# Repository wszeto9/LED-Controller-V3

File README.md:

# LED-Controller-V3
Version 3 of a easy-to-deploy, low-cost PCBA to control LED lights over Wi-Fi. Designed for use at MIT's East Campus REX event to light up large forts and structures at distances of over 28 ft.

[Interactive BOM](https://htmlpreview.github.io/?https://raw.githubusercontent.com/wszeto9/LED-Controller-V3/main/Documentation/bom/ibom.html)

[PDF Schematic](https://github.com/wszeto9/LED-Controller-V3/blob/main/PCB/LED_Controller_V3.pdf)

**Features:**

- All surface-mount components are basic components that can be placed with JLCPCB's SMT service
- All components that require hand-soldering are through-hole

- Power is transmitted through 14' long ethernet cables to simplify wiring

- Power Input is fused with Mini Blade Fuses

**High-Level Power Distribution Plan**

1. MIT Electric installs a Spider Box that is approximately 50 ft. away from the structure. The Spider Box has numerous 120V outlets that can be used to pull power for the lights.

2. Extension cords are ran from the Spider Box to the DJ Station, as well as other points on the structure as needed. 

3. Power supples (24V/16A, AC to DC) are wired up to the extension cords at all locations that need power. 

4. Each node has a 24V to 5V DC-DC buck converter. This supplies the 5V for all microcontrollers. 

5. 24V and 5V are wired into the power distribution PCB

6. Ethernet cables are run between the power distrubution PCB and nodes. Each node consists of an LED Controller board(this project) and a strip of lights.

**Power Input** 

The Power Distrubution PCB has jumpers that determine the voltage that the LED Controller receives. The LED Power Voltage shall be the same as the LEDs' rated voltage. For instance, 12V Addressible LEDs need 12V Power. The Power Distribution PCB also distributes 5V through the same Ethernet cable. This powers the ESP for changing lighting configurations over Wi-Fi. 

**Fuses** 

This board fuses the LED Power to protect the traces and wires from potential shorts. It is suggested to populate the fuse with one that is rated for 1.5x its current consumption at full brightness. Please note, the RJ45 Connector is rated for 1.5A per connector, for a total of 4.5A for LED Power and 3A for 5V. For this reason, fuses shall not exceed 5A. 

**LED Indicators**

If the board is fully functional, the following LEDs should be continuously lit:

- VCC shall be lit if VCC is higher than 5V and 5V is present

- 5V shall be lit if 5V is present

- 3.3V shall be lit if the 3.3V LDO is populated and 3.3V is present

**Optional to Populate**
- The 5V Buck converter does not need to be populated if the distribution PCB supplies 5V. 

- The 3.3V LDO does not need to be populated if the MCU has a reliable 3.3V LDO built-in. In this case, remove R4 and jump R3.

**Pinouts and Outputs**

Follow the table to set the correct pins to control the LEDs. Both the Wemos D1 and S2 mini are compatable with the Control Board. 
| Wemos D1 GPIO Pin| S2 Mini GPIO Pin| Function |
| -----------------|-----------------| -------- |
| 4|33|Addressible LED 1|
| 5|35|Addressible LED 2|
|14|7 |Analog White
|12|9|Analog Blue
|13|11|Analog Red
|15|12|Analog Green

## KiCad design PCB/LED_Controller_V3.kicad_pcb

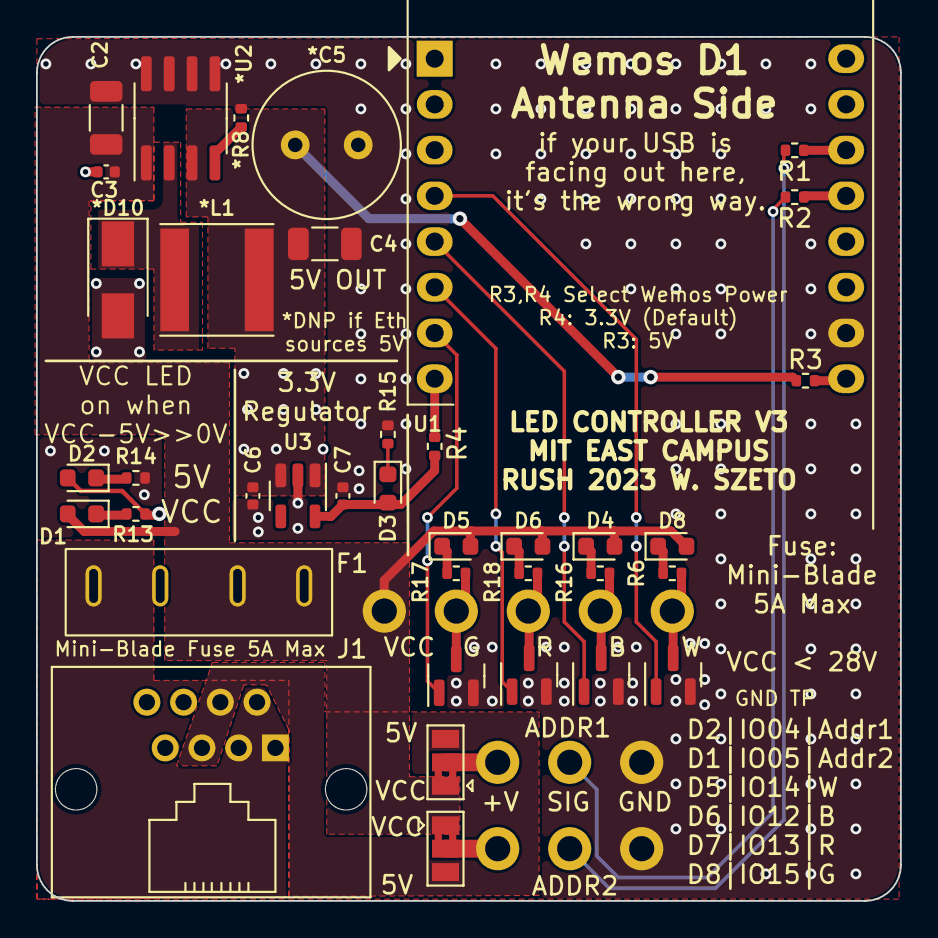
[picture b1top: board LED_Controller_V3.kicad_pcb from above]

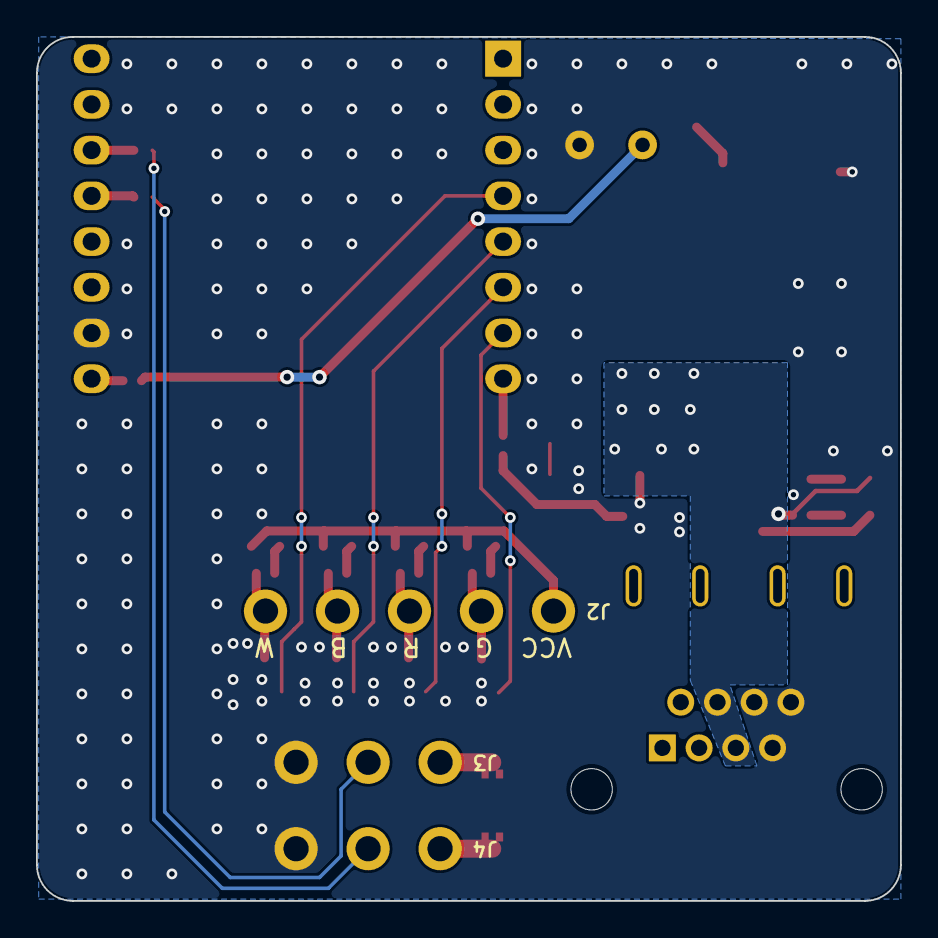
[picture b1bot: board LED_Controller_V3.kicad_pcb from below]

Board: 2 copper layers, 48.0 x 48.0 mm, 41 parts (3 on the bottom side), 30 nets.

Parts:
*C5: 180uF/35V; C_Radial_D8.0mm_H7.0mm_P3.50mm
*D10: SS210; D_SMA
*L1: 68uH/1A; L_Taiyo-Yuden_NR-60xx
*R8: 0R; R_0402_1005Metric
*U2: XL1509; SOIC-8_3.9x4.9mm_P1.27mm
C2, C4: 10uF/50V; C_1206_3216Metric
C3: 100nF/50V; C_0402_1005Metric
C6, C7: 10uF; C_0402_1005Metric
D1: LED_WHITE; LED_0603_1608Metric
D2: LED_RED; LED_0603_1608Metric
D3: LED_GREEN; LED_0603_1608Metric
D4: LED_B; LED_0603_1608Metric
D5: LED_G; LED_0603_1608Metric
D6: LED_R; LED_0603_1608Metric
D8: LED_W; LED_0603_1608Metric
F1: Fuse; XF-506P
J1: RJ45; RJ45_5501-88011111
J2: GRBW; 1x05_16AWG_Wire2Board
J3, J4: Conn_01x03; 1x03_16AWG_Wire2Board
JP1, JP2: VoltageSelector; SolderJumper-3_P1.3mm_Bridged2Bar12_Pad1.0x1.5mm
Q1, Q2, Q3, Q4: AO3400A; SOT-23
R1, R2: 220R; R_0402_1005Metric
R3: DNP; R_0402_1005Metric
R4: 0R; R_0402_1005Metric
R6, R16, R17, R18: 8.2k; R_0402_1005Metric
R13: 2K; R_0402_1005Metric
R14: 1K; R_0402_1005Metric
R15: 330R; R_0402_1005Metric
U1: WeMos_D1_mini; WEMOS_D1_mini_light
U3: XC6210B332MR; SOT-23-5

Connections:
+3V3: C7.1, D3.2 (A), R4.1, U3.5 (VOUT)
+5V: *C5.1, *L1.2, *U2.3 (FB), C4.2, C6.1, D2.2 (A), J1.4, J1.5, JP1.3 (B), JP2.3 (B), R3.1, R13.2, U3.1 (VIN), U3.3 (CE)
/ARGB1: J3.2, R2.2
/ARGB2: J4.2, R1.2
/B: J2.4, Q1.3 (D), R16.2
/B_SIG: Q1.1 (G), U1.5 (MISO/D6)
/G: J2.2, Q3.3 (D), R17.2
/G_SIG: Q3.1 (G), U1.7 (CS/D8)
/R: J2.3, Q2.3 (D), R18.2
/R_SIG: Q2.1 (G), U1.6 (MOSI/D7)
/W: J2.5, Q4.3 (D), R6.2
/W_SIG: Q4.1 (G), U1.4 (SCK/D5)
GND: *C5.2, *D10.2 (A), *R8.2, *U2.5 (GND), *U2.6 (GND), *U2.7 (GND), *U2.8 (GND), C2.2, C3.1, C4.1, C6.2, C7.2, J1.6, J1.7, J1.8, J3.3, J4.3, Q1.2 (S), Q2.2 (S), Q3.2 (S), Q4.2 (S), R14.2, R15.2, U1.10 (GND), U3.2 (GND)
unnamed: D1.1 (K), R13.1
unnamed: D2.1 (K), R14.1
unnamed: D3.1 (K), R15.1
unnamed: D4.1 (K), R16.1
unnamed: D5.1 (K), R17.1
unnamed: D6.1 (K), R18.1
unnamed: D8.1 (K), R6.1
unnamed: *D10.1 (K), *L1.1, *U2.2 (OUT)
unnamed: F1.2, J1.1, J1.2, J1.3
unnamed: J3.1, JP1.2 (C)
unnamed: J4.1, JP2.2 (C)
unnamed: R1.1, U1.14 (SCL/D1)
unnamed: R2.1, U1.13 (SDA/D2)
unnamed: R3.2, U1.9 (5V)
unnamed: *R8.1, *U2.4 (nEN)
unnamed: R4.2, U1.8 (3V3)
VCC: *U2.1 (VIN), C2.1, C3.2, D1.2 (A), D4.2 (A), D5.2 (A), D6.2 (A), D8.2 (A), F1.1, J2.1, JP1.1 (A), JP2.1 (A)

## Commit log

2023-01-29 Moved documentation to its own folder
2023-01-29 fixed broken link for sch
2023-01-29 Added pcb picture
2023-01-29 Changed Lighting Layout image to have white background
    Changed Lighting Layout image to have white background in order to be viewable on dark mode
2023-06-11 added step file
